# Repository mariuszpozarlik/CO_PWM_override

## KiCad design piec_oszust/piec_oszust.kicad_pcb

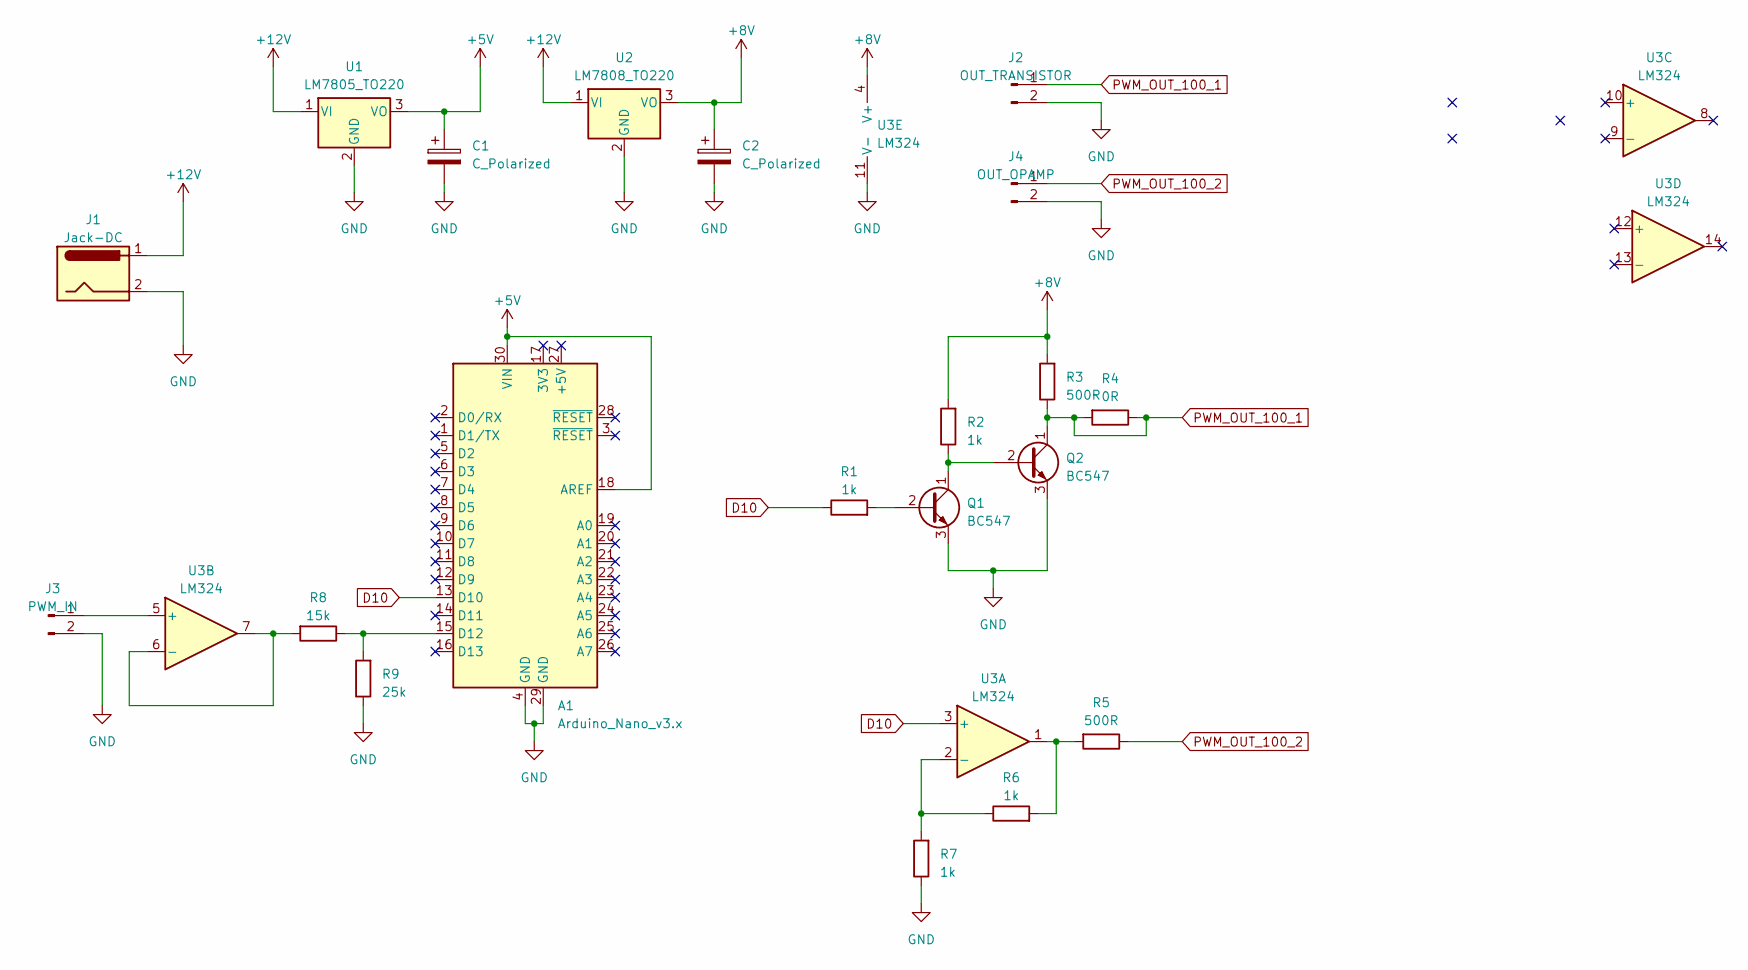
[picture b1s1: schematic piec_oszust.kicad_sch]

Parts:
A1: Arduino_Nano_v3.x; Arduino_Nano
C1, C2: C_Polarized; CP_Radial_D8.0mm_P5.00mm
J1: Jack-DC; BarrelJack_CUI_PJ-063AH_Horizontal
J2: OUT_TRANSISTOR; PinSocket_1x02_P2.54mm_Vertical
J3: PWM_IN; PinSocket_1x02_P2.54mm_Vertical
J4: OUT_OPAMP; PinSocket_1x02_P2.54mm_Vertical
Q1, Q2: BC547; TO-92_Inline
R1, R2, R6, R7: 1k; R_Axial_DIN0204_L3.6mm_D1.6mm_P7.62mm_Horizontal
R3, R5: 500R; R_Axial_DIN0204_L3.6mm_D1.6mm_P7.62mm_Horizontal
R4: 0R; R_Axial_DIN0204_L3.6mm_D1.6mm_P7.62mm_Horizontal
R8: 15k; R_Axial_DIN0204_L3.6mm_D1.6mm_P7.62mm_Horizontal
R9: 25k; R_Axial_DIN0204_L3.6mm_D1.6mm_P7.62mm_Horizontal
U1: LM7805_TO220; TO-220-3_Vertical
U2: LM7808_TO220; TO-220-3_Vertical
U3: LM324; DIP-14_W7.62mm

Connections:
+5V: A1.18 (AREF), A1.30 (VIN), C1.1, U1.3 (VO)
+8V: C2.1, R2.2, R3.2, U2.3 (VO), U3.4 (V+)
+12V: J1.1, U1.1 (VI), U2.1 (VI)
D10: A1.13 (D10), R1.1, U3.3 (+)
GND: A1.4 (GND), A1.29 (GND), C1.2, C2.2, J1.2, J2.2, J3.2, J4.2, Q1.3 (E), Q2.3 (E), R7.1, R9.1, U1.2 (GND), U2.2 (GND), U3.11 (V-)
unnamed: A1.15 (D12), R8.1, R9.2
unnamed: J3.1, U3.5 (+)
unnamed: Q1.2 (B), R1.2
unnamed: Q1.1 (C), Q2.2 (B), R2.1
unnamed: R5.2, R6.2, U3.1
unnamed: R6.1, R7.2, U3.2 (-)
unnamed: R8.2, U3.6 (-), U3.7
PWM_OUT_100_1: J2.1, Q2.1 (C), R3.1, R4.1, R4.2
PWM_OUT_100_2: J4.1, R5.1

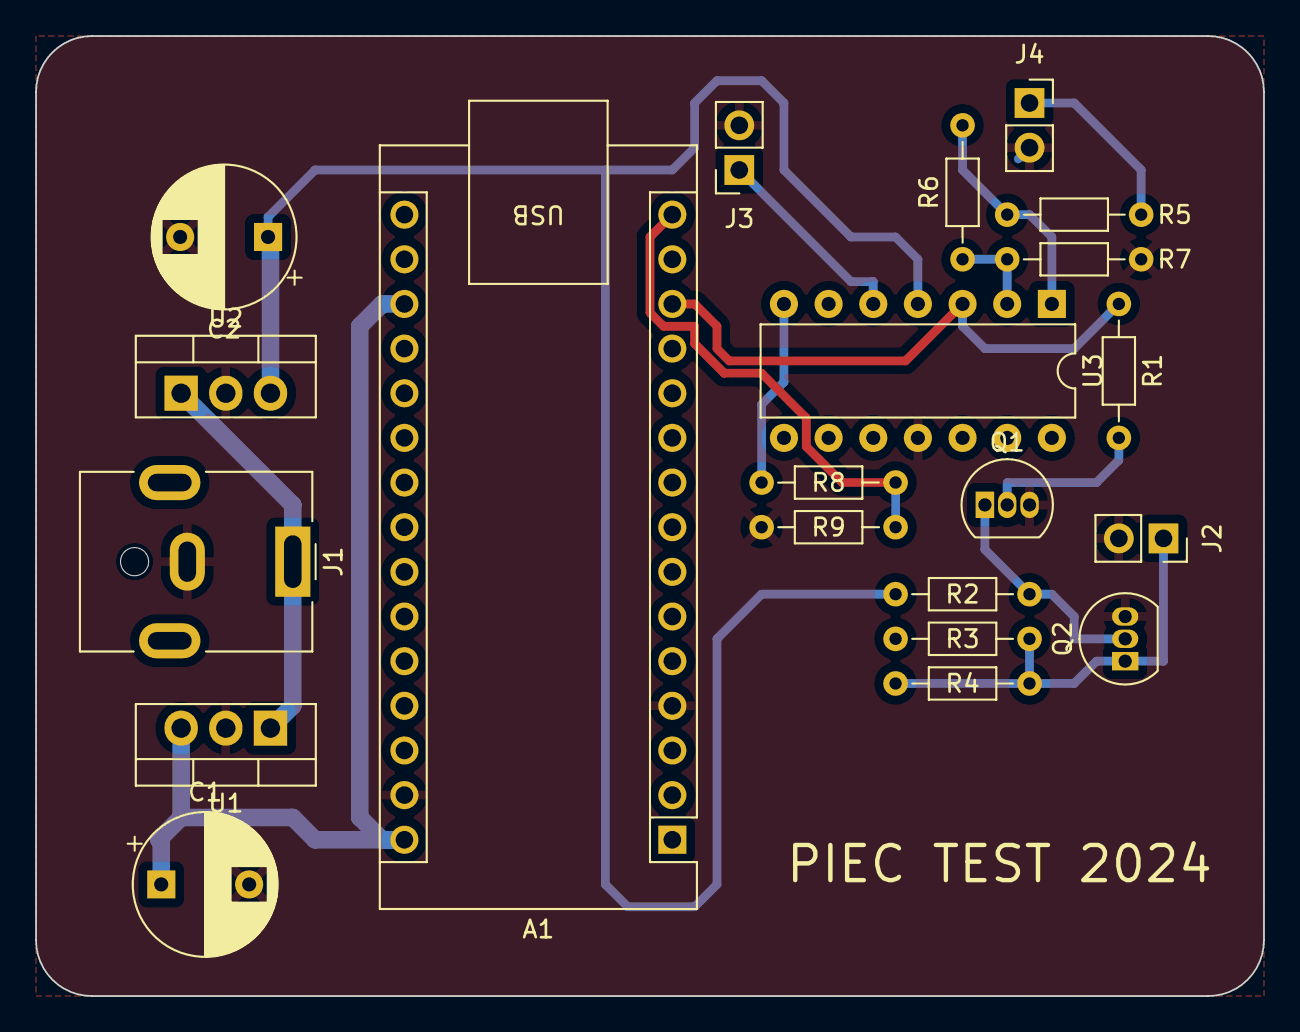
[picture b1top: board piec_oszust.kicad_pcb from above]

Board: 2 copper layers, 69.9 x 54.6 mm, 21 parts (0 on the bottom side), 14 nets.

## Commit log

2024-03-02 updates, gerber, drill, map files added
2024-03-03 missing connection
